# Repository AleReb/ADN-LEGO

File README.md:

# ADN LEGO

Simulador didactico de lector/secuenciador de ADN hecho con una placa ESP32-S3 SuperMini, un sensor de color TCS34725, una pantalla OLED I2C, botones de control y un motor paso a paso. La muestra fisica se representa con piezas o marcas de color que pasan frente al sensor; cada color se traduce a una base de ADN.

## Idea del proyecto

El equipo no secuencia ADN real. Simula el principio de lectura por posiciones: el motor mueve una tira o mecanismo LEGO una distancia fija, el sensor detecta el color en la nueva posicion y el firmware lo convierte en una base:

| Color | Base |
| --- | --- |
| Azul | A |
| Rojo | T |
| Verde | G |
| Amarillo | C |
| Sin lectura clara | N |

La secuencia se acumula en memoria, se muestra en la OLED y se imprime por el monitor Serial.

## Estructura del repositorio

```text
.
|-- lego_adnV2/
|   `-- lego_adnV2.ino      # Firmware Arduino/ESP32
`-- pcb/
    |-- adn_Lego.sch        # Esquematico EAGLE
    |-- adn_Lego.brd        # PCB EAGLE
    |-- adn_Lego_*.job      # Jobs/CAM de EAGLE
    `-- eagle.epf           # Proyecto EAGLE
```

## Hardware documentado en el PCB

El esquematico `pcb/adn_Lego.sch` contiene estos bloques:

| Nombre en PCB | Funcion |
| --- | --- |
| `ESP32S3_SUPERMINI` | Controlador principal |
| `U$1` | Pantalla OLED 128x64 I2C |
| `RGB` | Conector I2C para sensor de color TCS34725 |
| `I2C2` | Segundo conector I2C auxiliar |
| `SV1` | Conector de motor |
| `SW1` | Boton reset/nueva secuencia |
| `SW2` | Boton retroceder |
| `SW3` | Boton avanzar/leer base |
| `EXP/S3` | Header de expansion |

## Mapa de pines usado por el firmware

| Senal | GPIO ESP32-S3 |
| --- | --- |
| Motor IN1 | GPIO4 |
| Motor IN2 | GPIO3 |
| Motor IN3 | GPIO2 |
| Motor IN4 | GPIO1 |
| Boton reset | GPIO5 |
| Boton retroceder | GPIO6 |
| Boton avanzar | GPIO7 |
| I2C SDA | GPIO8 |
| I2C SCL | GPIO9 |

El firmware fuerza `Wire.begin(8, 9)` para coincidir con el PCB.

## Pinout de conectores del PCB

| Conector | Pin | Senal |
| --- | --- | --- |
| `SV1` motor | 1 | Motor IN1 / GPIO4 |
| `SV1` motor | 2 | Motor IN2 / GPIO3 |
| `SV1` motor | 3 | Motor IN3 / GPIO2 |
| `SV1` motor | 4 | Motor IN4 / GPIO1 |
| `SV1` motor | 5 | GND |
| `SV1` motor | 6 | 5V |
| `RGB` sensor TCS34725 | 1 | SCL / GPIO9 |
| `RGB` sensor TCS34725 | 2 | SDA / GPIO8 |
| `RGB` sensor TCS34725 | 3 | GND |
| `RGB` sensor TCS34725 | 4 | 5V |
| `I2C2` auxiliar | 1 | SCL / GPIO9 |
| `I2C2` auxiliar | 2 | SDA / GPIO8 |
| `I2C2` auxiliar | 3 | GND |
| `I2C2` auxiliar | 4 | 5V |
| `EXP/S3` | 1 | SDA / GPIO8 |
| `EXP/S3` | 2 | SCL / GPIO9 |
| `EXP/S3` | 3 | GPIO10 |
| `EXP/S3` | 4 | GPIO11 |
| `EXP/S3` | 5 | GPIO12 |
| `EXP/S3` | 6 | GPIO13 |
| `EXP/S3` | 7 | 3V3 |
| `EXP/S3` | 8 | GND |
| `EXP/S3` | 9 | 5V |

## Dependencias de Arduino

Instalar desde el Library Manager:

- `Adafruit TCS34725`
- `Adafruit BusIO`
- `U8g2`

Seleccionar una placa compatible con ESP32-S3 SuperMini en el core de ESP32 para Arduino.

## Uso

1. Abrir `lego_adnV2/lego_adnV2.ino` en Arduino IDE.
2. Seleccionar la placa ESP32-S3 y el puerto correcto.
3. Cargar el sketch.
4. Abrir el monitor Serial a `115200` baudios.
5. Colocar la tira LEGO o plantilla de colores frente al lector.
6. Pulsar avanzar para mover una posicion y leer una base.
7. Pulsar retroceder para volver una posicion y borrar la ultima base.
8. Pulsar reset para iniciar una nueva secuencia.

La salida Serial tiene este formato:

```text
>nueva_secuencia
Base 1: A | Secuencia: A
Base 2: T | Secuencia: AT
Base 3: G | Secuencia: ATG
```

## Cambios realizados al firmware

- Se reemplazo la lectura suelta de colores por un flujo de secuenciacion.
- Se agrego acumulacion de secuencia hasta 64 bases.
- Se agrego salida Serial con indice de base y secuencia completa.
- Se corrigio el I2C para usar SDA `GPIO8` y SCL `GPIO9`, como indica el PCB.
- Se eliminaron dependencias no usadas (`Stepper`, `AsyncStepperLib`, `cstring`).
- Se agrego liberacion de bobinas del motor despues de cada movimiento.
- Se normalizo la clasificacion de color usando proporciones RGB, menos sensible a cambios de brillo que valores absolutos.
- Se agrego lectura `N` cuando el color no es confiable.

## Ajustes necesarios para que funcione bien como simulador

Estos parametros estan al inicio de `lego_adnV2.ino` y probablemente deben calibrarse en el prototipo fisico:

| Parametro | Valor actual | Que ajustar |
| --- | --- | --- |
| `stepsPerBase` | `845` | Pasos entre dos colores consecutivos de la tira LEGO |
| `stepDelayMs` | `1` | Velocidad del motor; subir si pierde pasos |
| `readSettleMs` | `250` | Pausa despues de mover antes de leer color |
| `minClearToRead` | `250` | Umbral minimo de luz para aceptar lectura |
| Reglas de `identifyBase()` | Umbrales RGB normalizados | Afinar si un color se confunde con otro |

## Mejoras recuperadas para una futura version `lego_adn_v3`

Al comparar el firmware actual con la documentacion del codigo antiguo, las mejoras que conviene recuperar o implementar como un todo son:

| Mejora | Origen / motivo | Implementacion esperada en `lego_adn_v3` |
| --- | --- | --- |
| Modo automatico por marcas negras | La documentacion antigua describia busqueda de inicio, lectura continua y fin por bloques negros, pero el sketch actual no lo implementa | Agregar una maquina de estados: buscar inicio, avanzar por bases, validar color, detectar fin y publicar secuencia completa |
| Deteccion robusta de inicio/fin | Los bloques negros funcionaban como control de secuencia | Contar varias lecturas negras consecutivas antes de declarar inicio o fin, para evitar falsos positivos |
| Reintentos de lectura de color | El codigo actual toma una lectura despues del movimiento | Tomar varias muestras RGB/C por posicion, descartar lecturas debiles y clasificar con promedio o mediana |
| Calibracion guiada | Los rangos antiguos eran fijos y dependian del prototipo fisico | Crear modo de calibracion para Azul/Rojo/Verde/Amarillo/Negro y clasificar por distancia al color calibrado |
| Estados de operacion | La documentacion antigua proponia flags como sensorReady, displayReady, manualMode y autoMode | Mantener estado explicito del sistema y mostrarlo en OLED/Serial |
| Debounce por tiempo | El firmware actual usa flags de flanco, suficiente pero sensible a rebote mecanico | Usar `millis()` para debounce de botones y para evitar dobles lecturas |
| Mejor manejo de fallos | El sketch actual muestra error si no encuentra el TCS34725, pero sigue dependiendo de lecturas validas | Reportar estado de sensor/pantalla, permitir reintentos y evitar bloquear el flujo completo |
| Salida Serial mas estructurada | El codigo actual imprime texto humano; para analisis posterior puede ser util un formato estable | Agregar lineas tipo CSV o eventos: `BASE,index,base,sequence`, `STATE,...`, `ERROR,...` |
| Pantalla con modo docente | La idea educativa pide ver color, base, valores RGB y secuencia | Alternar o compactar vistas OLED: lectura actual, estado, largo y secuencia |

La proxima implementacion deberia vivir en una carpeta separada `lego_adn_v3/`, manteniendo `lego_adnV2/` como version manual estable.

## Notas del PCB

- El PCB usa I2C compartido para la OLED y el sensor TCS34725.
- La OLED esta en `3V3`.
- El conector `RGB` aparece alimentado desde `5V`; verificar el modulo TCS34725 usado. Muchos modulos toleran `3V3-5V`, pero si el sensor no tiene regulador o conversores de nivel, conviene alimentarlo a `3V3`.
- Los botones estan cableados a GND y el firmware usa `INPUT_PULLUP`.
- El motor requiere una etapa driver externa si el conector `SV1` va a bobinas o a un motor tipo 28BYJ-48. No se debe alimentar un motor directamente desde GPIO del ESP32.

## Estado actual

El proyecto queda preparado como simulador funcional de secuenciador: mueve por pasos, lee colores, traduce a bases A/T/G/C/N, muestra la lectura y construye una secuencia. La precision final depende de la calibracion mecanica de `stepsPerBase`, la iluminacion alrededor del sensor y el contraste de los colores usados.

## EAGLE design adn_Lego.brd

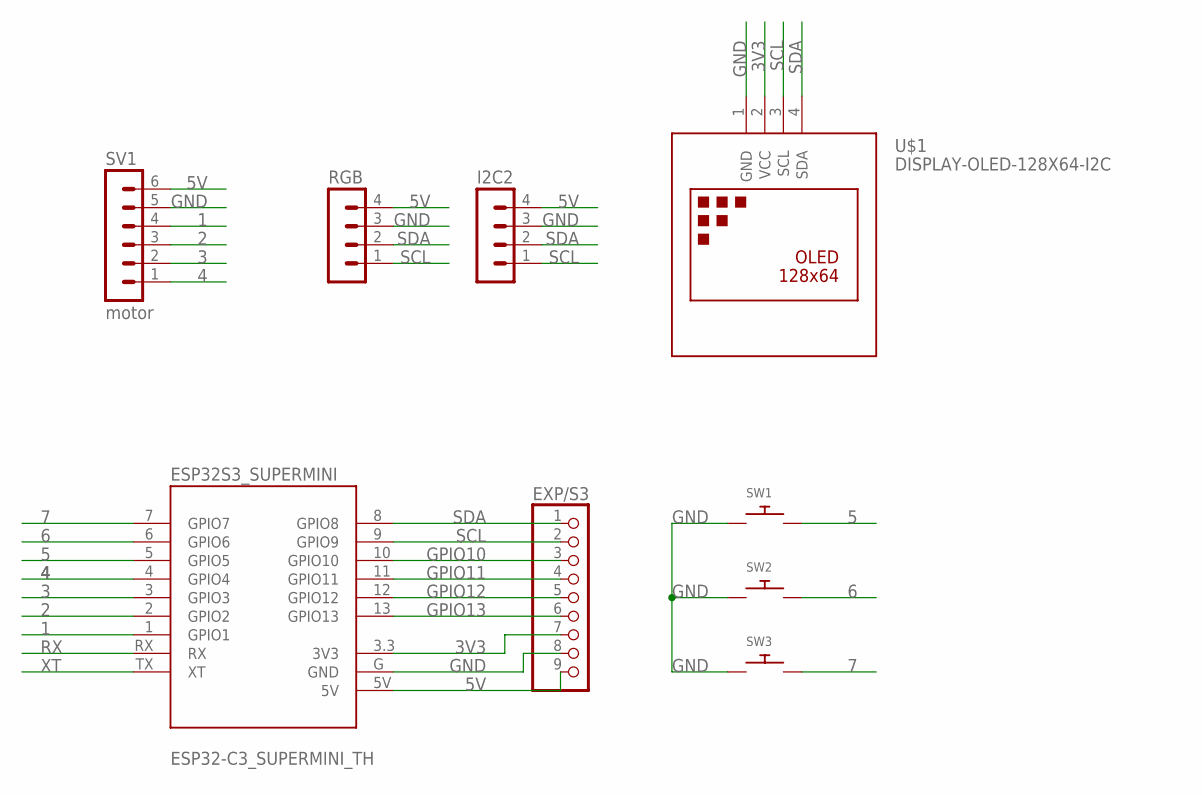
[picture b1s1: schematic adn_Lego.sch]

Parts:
ESP32S3_SUPERMINI: ESP32-C3_SUPERMINI_TH; MODULE_ESP32-C3_SUPERMINI_TH
EXP/S3: PINHD-1X9; 1X09
I2C2: MA04-1
RGB: MA04-1
SV1: motor; MA06-1
SW1, SW2, SW3: SWITCH_PUSHBUTTONEVQ-PE; TACT_PANA-EVQ
U$1: DISPLAY-OLED-128X64-I2C

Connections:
1: ESP32S3_SUPERMINI.1 (GPIO1), SV1.4
2: ESP32S3_SUPERMINI.2 (GPIO2), SV1.3
3: ESP32S3_SUPERMINI.3 (GPIO3), SV1.2
3V3: ESP32S3_SUPERMINI.3.3 (3V3), EXP/S3.7, U$1.2 (VCC)
4: ESP32S3_SUPERMINI.4 (GPIO4), SV1.1
5: ESP32S3_SUPERMINI.5 (GPIO5), SW1.P$2
5V: ESP32S3_SUPERMINI.5V, EXP/S3.9, I2C2.4, RGB.4, SV1.6
6: ESP32S3_SUPERMINI.6 (GPIO6), SW2.P$2
7: ESP32S3_SUPERMINI.7 (GPIO7), SW3.P$2
GND: ESP32S3_SUPERMINI.G (GND), EXP/S3.8, I2C2.3, RGB.3, SV1.5, SW1.P$1, SW2.P$1, SW3.P$1, U$1.1 (GND)
GPIO10: ESP32S3_SUPERMINI.10 (GPIO10), EXP/S3.3
GPIO11: ESP32S3_SUPERMINI.11 (GPIO11), EXP/S3.4
GPIO12: ESP32S3_SUPERMINI.12 (GPIO12), EXP/S3.5
GPIO13: ESP32S3_SUPERMINI.13 (GPIO13), EXP/S3.6
RX: ESP32S3_SUPERMINI.RX
SCL: ESP32S3_SUPERMINI.9 (GPIO9), EXP/S3.2, I2C2.1, RGB.1, U$1.3 (SCL)
SDA: ESP32S3_SUPERMINI.8 (GPIO8), EXP/S3.1, I2C2.2, RGB.2, U$1.4 (SDA)
XT: ESP32S3_SUPERMINI.TX (XT)

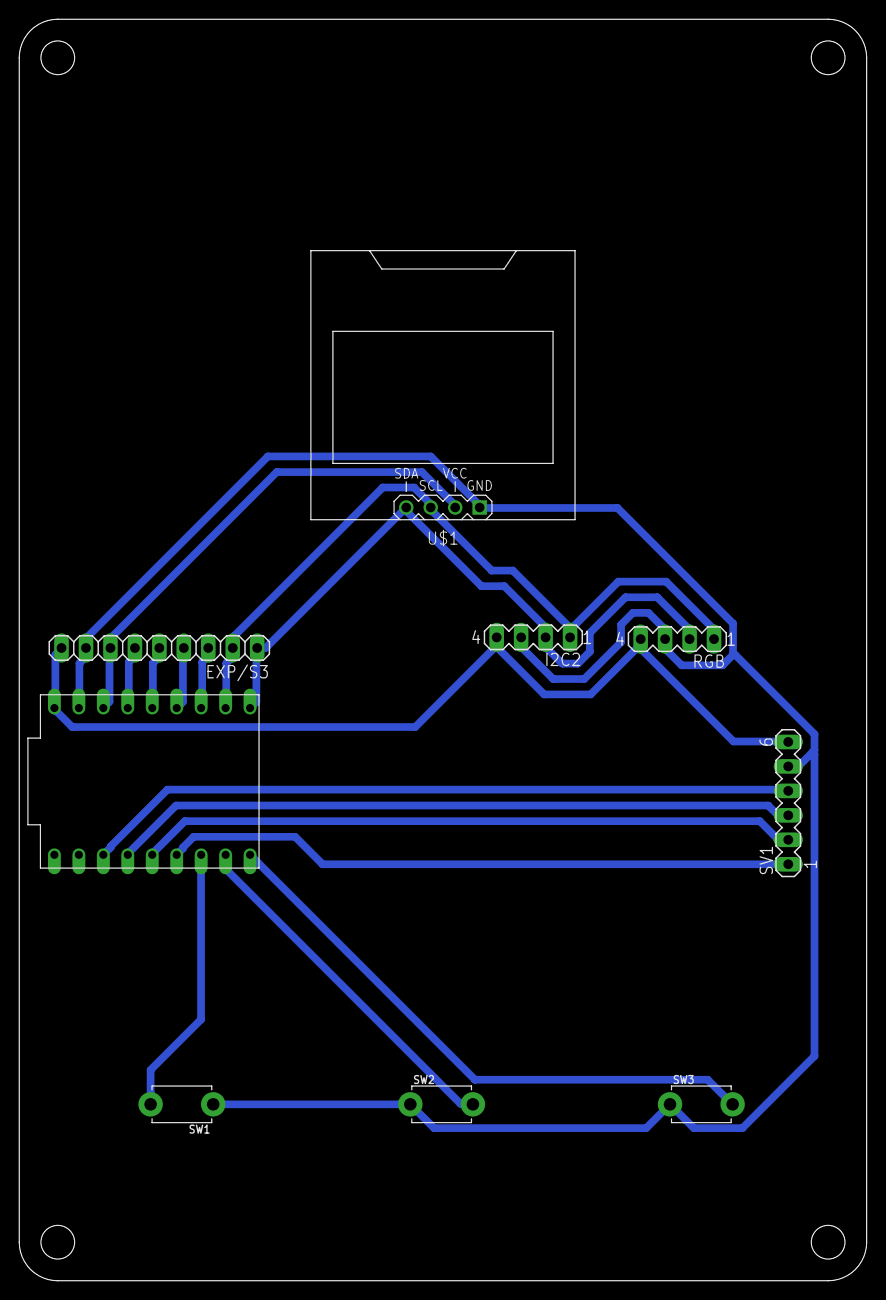
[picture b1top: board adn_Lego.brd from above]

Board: 2 copper layers, 88.0 x 131.0 mm, 9 parts (0 on the bottom side), 16 nets.

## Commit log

2026-05-07 Refactor code structure for improved readability and maintainability
2026-05-07 Add initial implementation of motor control and color detection features
2026-05-08 Add Fusion synchronization support and update README for ADN LEGO project
    - Updated ADN LEGO PCB file to include Fusion sync attributes.
    - Added warning notes regarding Fusion synchronization and URN support in EAGLE.
    - Removed unused library reference from eagle.epf.
    - Adjusted screen resolution in eagle.epf for better display.
    - Created README.md to document project details, hardware structure, pin mapping, dependencies, usage instructions, firmware changes, and PCB notes.
2026-05-09 Actualiza documentacion de hardware y mejoras v3

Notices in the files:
parts and their libraries:
diy-modules: Released under the Creative Commons Attribution 4.0 International License: http://creativecommons.org/licenses/by/4.0
